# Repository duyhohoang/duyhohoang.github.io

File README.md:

# Hardware Lab portfolio

Existing black-and-pink portfolio for PCB Design, Embedded Systems and IoT. Next.js App Router, React, TypeScript and Motion. Self-hosted fonts and local imagery; no backend, API, database, server actions or runtime Node server.

## Local development

Use Node **24.19.0** (`.node-version`) and **pnpm 11.25.0** (`packageManager`).

```sh
pnpm install --frozen-lockfile
pnpm dev
```

Development: http://127.0.0.1:3000. For production:

```sh
pnpm lint
pnpm test
pnpm build
pnpm check:export
pnpm preview
```

Static preview: http://127.0.0.1:3001. Deploy only `out/`. `next.config.ts` already preserves export, trailing slashes, unoptimized local images and disabled framework header. The postbuild helper preserves Windows-generated Next segment payload aliases; it is harmless on Linux.

## Public configuration

Copy `.env.example` to `.env.local` if overriding defaults. `src/data/contact.ts` contains the owner-provided public email, `hoangduy2206.ute@gmail.com`. `NEXT_PUBLIC_CONTACT_EMAIL` overrides it; an explicitly empty value disables composition and shows a configuration warning. Public variables are embedded at build time and must never contain secrets.

The contact form validates fields and composes a safely encoded `mailto:` draft. Visitors finish sending in their own email app. No delivery is performed or reported by this website. A direct **Send Email** link works without JavaScript; form submission is disabled until hydration to avoid leaking form fields into a GET URL.

Set `NEXT_PUBLIC_SITE_URL` to your real HTTPS Pages origin or custom domain and rebuild before enabling search indexing. Without it, the local preview intentionally emits noindex/disallow and localhost canonical/sitemap URLs.

## GitHub Pages production

The selected address is **https://duyhohoang.github.io/**, published from repository `duyhohoang.github.io`. The included GitHub Actions workflow builds and deploys only `out/` on main pushes. Enable **Settings → Pages → Source: GitHub Actions** in that repository. See [DEPLOY.md](DEPLOY.md) for setup and validation.

## Alternative Cloudflare deployment

For the current Workers project, `wrangler.jsonc` explicitly serves static files from `out/`; build with `pnpm build` and deploy with `npx wrangler@4.151.3 deploy`. No OpenNext migration or runtime server is needed.

For the alternative Pages workflow, see [DEPLOY.md](DEPLOY.md) for GitHub connection, build settings, free Pages address, custom domain and automatic deploys. Use the **Next.js (Static HTML Export)** preset, `pnpm build`, output `out`, production branch `main`. This is prepared locally, not publicly deployed.

## Implementation and validation

- `src/components/PortfolioHome.tsx`: existing homepage sections and content.
- `src/components/backgrounds/CircuitBackground.tsx`: SVG decoration; visibility-aware CSS pulses, static on mobile/reduced motion.
- `src/hooks/usePortfolioMotion.ts`: one shared reveal observer and finite animations, with lifecycle cleanup.
- `src/components/ContactForm.tsx`, `src/lib/contact.ts`: validated email draft composition.
- `src/data/portfolio-media.ts`: replaceable local portrait and hardware media.
- `scripts/review-fidelity.mjs`: twelve reference-sized production screenshots.
- `scripts/test-animations.mjs`: production interactions, motion, six viewport widths, navigation cleanup and no-JS checks.
- `docs/PHASE4-REPORT.md`: validation evidence and remaining limitations.

Project studies remain illustrative, with validation status identified. No employment, education, manufacturing results or client metrics have been invented.

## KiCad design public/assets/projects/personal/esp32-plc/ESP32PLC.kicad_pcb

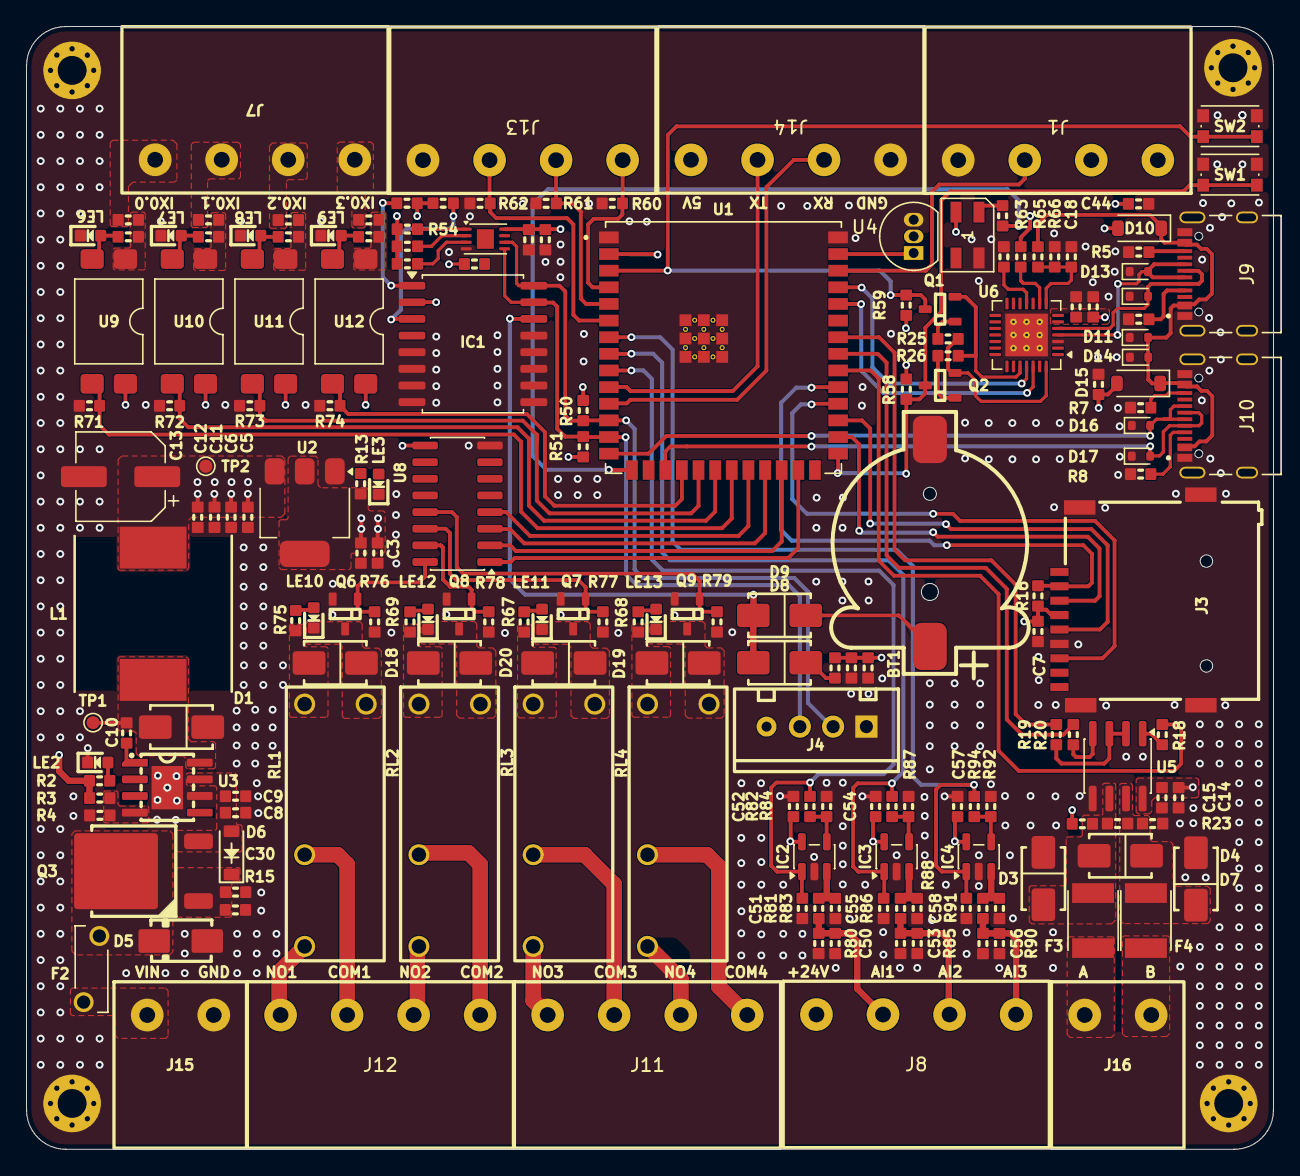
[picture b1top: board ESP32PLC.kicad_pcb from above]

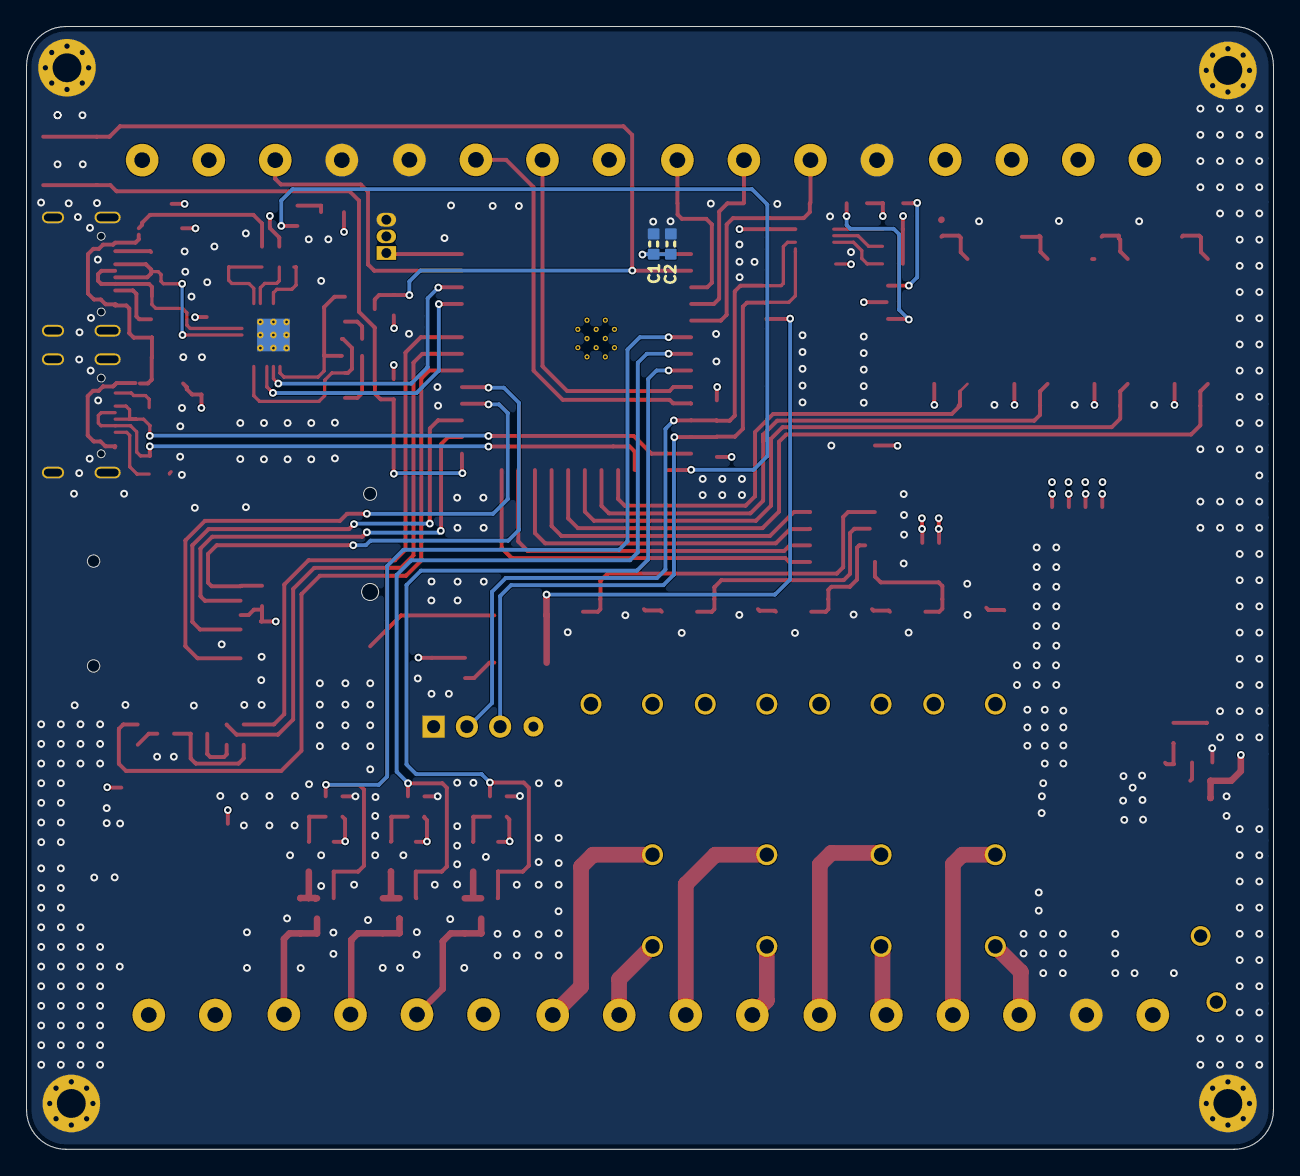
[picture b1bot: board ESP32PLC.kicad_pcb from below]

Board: 4 copper layers, 95.2 x 85.7 mm, 190 parts (2 on the bottom side), 117 nets.

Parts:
BT1: Battery_Cell; BatteryHolder_CR1220
C1, C3, C6, C16, C41, C43, C46, C47, C48, C49, C50, C51, C53, C55, C56, C58: 100nF/0603/50V; C_0603
C2, C4, C5, C17: 10uF/0603/6.3V; C_0603
C7, C15: 100nF/50V/0603; C_0603
C8, C9: 4.7uF/50V/0603; C_0603
C10, C12: 10uF/50V/0603; C_0603
C11, C14: 10uF/6.3V/0603; C_0603
C13: 220uF/6.3V/6.3x5.4; CP_Elec_6.3x5.4
C18: 1uF/0603/6.3V; C_0603
C30, C40, C42, C52, C54, C57: 1uF/0603/50V; C_0603
C44, C45: 10uF/0603/50V; C_0603
D1: SS54/5A/40V; D_SMA_TVS
D2: SK6812MINI; LED_SK6812MINI_PLCC4_3.5x3.5mm_P1.75mm
D3, D4, D7: D_TVS; D_SMA_TVS
D5: SMAJ281-E3/61; D_SMA
D6: BZT52H-C5V1; SOD-123
D8, D9, D18, D19, D20, D21: D_Diode; D_SMA_TVS
D10, D15: D_Schottky; D_SOD-123
D11, D12, D13, D14, D16, D17: LESD5D5.0CT1G; D_SOD-523
F2: RUEF250/30V/2.5A; FUSRR505W81L660T250H1360
F3, F4: Polyfuse; FUSER_MF-MSMF075_24-2
H1, H2, H3, H4: MountingHole_Pad; MountingHole_2.2mm_M2_Pad_Via
IC1: RTC_DS3231M; SOIC-16W_7.5x10.3mm_P1.27mm
IC2, IC3, IC4: TP5551-TR; SOT-23-5
J1, J7, J8, J11, J12, J13, J14: Screw_Terminal_01x04; KF-5.08-4P
J3: Micro_SD_Card_Det1; MicroSD_Socket_9P
J4: Conn_01x04_Pin; Conn_XH-P2.54mm-4P
J9, J10: TYPE-C-31-M-12; HRO_TYPE-C-31-M-12
J15, J16: Screw_Terminal_01x02; KF-5.08-2P
L1: 22uH/CDRH127-220; INDPM120120X800N
LE2, LE3, LE6, LE7, LE8, LE9, LE10, LE11, LE12, LE13: RED/0603; LED_0603
Q1, Q2: NPN; SOT23-3
Q3: P_Mosfet; TO-252-2
Q6, Q7, Q8, Q9: N_Mosfet; SOT23-3
R2, R13, R67, R68, R69, R75: 1K/0603/1%; R_0603
R3, R15, R16, R21, R23, R24, R25, R26, R58, R59, R63, R64, R71, R72, R73, R74, R80, R85, R90: 10K/0603/1%; R_0603
R4: 3.3K/0603/1%; R_0603
R5, R6, R7, R8: 5.1K/0603/1%; R_0603
R9, R10, R11, R12: 4.7K/0603/1%; R_0603
R17: 0R/0603/1%; R_0603
R18, R19, R20, R22: 120R/0603/1%; R_0603
R50, R51, R52, R53, R54, R55, R56, R57: 4K7/0603/1%; R_0603
R60, R61, R62: 165R/0603/1%; R_0603
R65: 22.1R/0603/50V; R_0603
R66: 47.5K/0603/50V; R_0603
R76, R77, R78, R79: 1M/0603/1%; R_0603
R81, R82, R83, R84, R86, R87, R88, R89, R91, R92, R93, R94: 100K/0603/1%; R_0603
RL1, RL2, RL3, RL4: Relay_G5NB-1A-E_DC5; Relay_G5NB-1A-E DC5
SW1, SW2: SW_Push; SW_Push_1P1T_NO_CK_KMR2
TP1, TP2: TestPoint; TestPoint_Pad_D1.0mm
U1: ESP32-S3-WROOM-1U-N8R8; XCVR_ESP32-S3-WROOM-1U-N8R8
U2: AMS1117-3.3; SOT-223-3_TabPin2
U3: TPS5430DDA; SOIC8E(EXPOSED PAD)
U4: LM35-LP; TO-92_Inline
U5: SP3485CN; SOIC-8_3.9x4.9mm_P1.27mm
U6: CP2102N-Axx-xQFN28; QFN-28-1EP_5x5mm_P0.5mm_EP3.25x3.25mm_ThermalVias
U7: 24LC512_IPC; DFN-8-1EP_3x2mm_P0.5mm_EP1.3x1.5mm
U8: ULN2003; SOIC-16_3.9x9.9mm_P1.27mm
U9, U10, U11, U12: Opto; SMDIP-4_W9.53mm_Clearance8mm

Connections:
+3.3V: C1.1, C2.1, C3.1, C4.1, C7.1, C14.1, C15.1, C16.1, C17.1, C42.1, C43.1, C52.1, C54.1, C57.1, D2.4 (VDD), IC2.5 (V+), IC3.5 (V+), IC4.5 (V+), J1.1, J1.2, J3.4 (VDD), R13.1, R16.1, R21.1, R58.1, R59.1, R63.1, U1.2 (3V3), U2.2 (VO), U5.8 (VCC), U6.6 (VDD), U6.7 (VREGIN), U7.8 (VCC), U9.4, U10.4, U11.4, U12.4
+5V: C5.1, C6.1, C11.1, C12.1, C13.1, C40.1, C41.1, C44.1, C45.1, D10.2, D15.2, D18.2, D19.2, D20.2, D21.2, IC1.2 (VCC), J4.4, J14.4, L1.2, R2.1, R3.1, R24.1, R50.1, R51.1, R52.2, R53.1, R54.1, R55.2, R56.2, R57.2, R67.1, R68.1, R69.1, R75.1, RL1.1, RL2.1, RL3.1, RL4.1, TP2.1 (1_1), U2.3 (VI), U4.2 (V_{OUT}), U8.9 (COM)
+24V: F2.2, J8.1, J15.1
/32K: IC1.1 (32KHZ), R53.2
/%IW0.0: J13.1, R60.1, U1.4 (IO4)
/%IW0.1: J13.2, R61.1, U1.5 (IO5)
/%IW0.2: J13.3, R62.1, U1.6 (IO6)
/%IX0.0: R71.1, U1.21 (IO13), U9.3
/%IX0.1: R72.1, U1.20 (IO12), U10.3
/%IX0.2: R73.1, U1.19 (IO11), U11.3
/%IX0.3: R74.1, U1.18 (IO10), U12.3
/%QX0.0: U1.25 (IO48), U8.1 (I1)
/%QX0.1: U1.24 (IO47), U8.2 (I2)
/%QX0.2: U1.23 (IO21), U8.3 (I3)
/%QX0.3: U1.22 (IO14), U8.4 (I4)
/A485: F3.2, J16.1
/AI1: C50.1, J8.2, R80.2, R81.1
/AI2: C53.1, J8.3, R85.2, R86.1
/AI3: C56.1, J8.4, R90.2, R91.1
/B485: F4.2, J16.2
/CC1: J9.A5 (CC1), R6.2
/CC2: J9.B5 (CC2), R5.2
/CC3: J10.A5 (CC1), R8.2
/CC4: J10.B5 (CC2), R7.2
/CHIP_PU: Q1.3 (C), R59.2, SW2.2, U1.3 (EN)
/CS: J3.2 (DAT3/CD), R16.2, U1.31 (IO38)
/DE_RE: R19.1, U1.34 (IO41)
/DTR: Q2.2 (E), R25.1, U6.28 (~DTR)
/GPIO0: Q2.3 (C), R58.2, SW1.2, U1.27 (IO0)
/GPIO1: U1.39 (IO1), U4.1 (+V_{S})
/GPIO2: J1.3, U1.38 (IO2)
/GPIO3: R17.1, U1.15 (IO3)
/GPIO7: C58.1, IC4.1 (OUT), R94.1, U1.7 (IO7)
/GPIO15: C55.1, IC3.1 (OUT), R89.1, U1.8 (IO15)
/GPIO16: C51.1, IC2.1 (OUT), R84.1, U1.9 (IO16)
/GPIO19: D17.2 (A2), J10.A7 (DN1), J10.B7 (DN2), U1.17 (IO9)
/GPIO20: D16.2 (A2), J10.A6 (DP1), J10.B6 (DP2), U1.14 (IO20)
/MISO: J3.7 (DAT0), U1.30 (IO37)
/MOSI: J3.3 (CMD), U1.28 (IO35)
/OUT1: J7.4, R9.1
/OUT2: J7.3, R10.1
/OUT3: J7.2, R11.1
/OUT4: J7.1, R12.1
/RGB_CTRL: D2.3 (DIN), R17.2
/RLAY1A: J12.1, RL1.3
/RLAY1B: J12.2, RL1.2
/RLAY2A: J12.3, RL2.3
/RLAY2B: J12.4, RL2.2
/RLAY3A: J11.1, RL3.3
/RLAY3B: J11.2, RL3.2
/RLAY4A: J11.3, RL4.3
/RLAY4B: J11.4, RL4.2
/RLY1: Q6.1 (G), R76.1, U8.16 (O1)
/RLY2: Q8.1 (G), R78.1, U8.15 (O2)
/RLY3: Q7.1 (G), R77.1, U8.14 (O3)
/RLY4: Q9.1 (G), R79.1, U8.13 (O4)
/RTS: Q1.2 (E), R26.1, U6.24 (~RTS)
/RX2: J14.2, U1.11 (IO18)
/RX485: R18.1, U1.32 (IO39)
/SCK: J3.5 (CLK), U1.29 (IO36)
/SCL: IC1.16 (SCL), J4.2, R50.2, U1.12 (IO8), U7.6 (SCL)
/SDA: IC1.15 (SDA), J4.3, R51.2, U1.13 (IO19), U7.5 (SDA)
/SQW: IC1.3 (~INT/SQW), R54.2
/TX2: J14.3, U1.10 (IO17)
/TX485: R20.1, U1.33 (IO40)
/U0RXD: U1.37 (TXD0), U6.25 (RXD)
/U0TXD: U1.36 (RXD0), U6.26 (TXD)
/USB_DN: D12.2 (A2), J9.A7 (DN1), J9.B7 (DN2), U6.5 (D-)
/USB_DP: D13.2 (A2), J9.A6 (DP1), J9.B6 (DP2), U6.4 (D+)
GND: BT1.2 (-), C1.2, C2.2, C3.2, C4.2, C5.2, C6.2, C7.2, C8.2, C9.2, C11.2, C12.2, C13.2, C14.2, C15.2, C16.2, C17.2, C18.2, C30.2, C40.2, C41.2, C42.2, C43.2, C44.2, C45.2, C50.2, C51.2, C52.2, C53.2, C54.2, C55.2, C56.2, C57.2, C58.2, D1.1, D2.2 (VSS), D3.1 (A1), D5.1 (A1), D7.2 (A2), D11.1 (A1), D12.1 (A1), D13.1 (A1), D14.1 (A1), D16.1 (A1), D17.1 (A1), H1.1 (1_1), H2.1 (1_1), H3.1 (1_1), H4.1 (1_1), IC1.5 (GND), IC1.6 (GND), IC1.7 (GND), IC1.8 (GND), IC1.9 (GND), IC1.10 (GND), IC1.11 (GND), IC1.12 (GND), IC1.13 (GND), IC2.2 (V-), IC3.2 (V-), IC4.2 (V-), J1.4, J3.6 (VSS), J3.10 (SHIELD), J4.1, J9.A1_B12 (GND), J9.B1_A12 (GND), J9.S1 (SHIELD), J9.S2 (SHIELD), J9.S3 (SHIELD), J9.S4 (SHIELD), J10.A1_B12 (GND), J10.B1_A12 (GND), J10.S1 (SHIELD), J10.S2 (SHIELD), J10.S3 (SHIELD), J10.S4 (SHIELD), J13.4, J14.1, J15.2, LE2.2, LE3.2, LE6.2, LE7.2, LE8.2, LE9.2, Q6.2 (S), Q7.2 (S), Q8.2 (S), Q9.2 (S), R4.2, R5.1, R6.1, R7.1, R8.1, R15.2, R23.2, R60.2, R61.2, R62.2, R64.2, R66.2, R71.2, R72.2, R73.2, R74.2, R76.2, R77.2, R78.2, R79.2, R80.1, R82.1, R83.2, R85.1, R87.1, R88.2, R90.1, R92.1, R93.2, SW1.1, SW2.1, U1.1 (GND), U1.40 (GND), U1.41_1 (GND), U1.41_2 (GND), U1.41_3 (GND), U1.41_4 (GND), U1.41_5 (GND), U1.41_6 (GND), U1.41_7 (GND), U1.41_8 (GND), U1.41_9 (GND), U2.1 (GND), U3.6 (GND), U3.9 (GNDPAD), U4.3 (GND), U5.5 (GND), U6.3 (GND), U6.29 (GND), U7.4 (GND), U8.8 (GND)
unnamed: BT1.1 (+), D9.1
unnamed: C46.1, R9.2, U9.1
unnamed: C46.2, LE6.1, U9.2
unnamed: C47.1, R10.2, U10.1
unnamed: C47.2, LE7.1, U10.2
unnamed: C48.1, R11.2, U11.1
unnamed: C48.2, LE8.1, U11.2
unnamed: C49.1, R12.2, U12.1
unnamed: C49.2, LE9.1, U12.2
unnamed: D3.2 (A2), D4.2 (A2), F3.1, R21.2, R22.1, U5.6 (A)
unnamed: D4.1 (A1), D7.1 (A1), F4.1, R22.2, R23.1, U5.7 (B)
unnamed: D5.2 (A2), F2.1, Q3.3 (D)
unnamed: C30.1, D6.2 (A), Q3.1 (G), R15.1
unnamed: C8.1, C9.1, D6.1 (K), Q3.2 (S), U3.7 (VIN)
unnamed: D8.1, R24.2
unnamed: D8.2, D9.2, IC1.14 (VBAT)
unnamed: IC2.3 (+IN), R81.2, R83.1
unnamed: IC2.4 (-IN), R82.2, R84.2
unnamed: IC3.3 (+IN), R86.2, R88.1
unnamed: IC3.4 (-IN), R87.2, R89.2
unnamed: IC4.3 (+IN), R91.2, R93.1
unnamed: IC4.4 (-IN), R92.2, R94.2
unnamed: LE2.1, R2.2
unnamed: LE3.1, R13.2
unnamed: LE10.1, R75.2
unnamed: LE11.1, R67.2
unnamed: LE12.1, R69.2
unnamed: LE13.1, R68.2
unnamed: Q1.1 (B), R25.2
unnamed: Q2.1 (B), R26.2
unnamed: D18.1, LE10.2, Q6.3 (D), RL1.4
unnamed: D19.1, LE11.2, Q7.3 (D), RL3.4
unnamed: D20.1, LE12.2, Q8.3 (D), RL2.4
unnamed: D21.1, LE13.2, Q9.3 (D), RL4.4
unnamed: C10.2, U3.1 (BOOT)
unnamed: C10.1, D1.2, L1.1, TP1.1 (1_1), U3.8 (PH)
unnamed: R3.2, R4.1, U3.4 (VSENSE)
unnamed: R19.2, U5.2 (~RE), U5.3 (DE)
unnamed: R20.2, U5.4 (DI)
unnamed: R18.2, U5.1 (RO)
unnamed: C18.1, R65.2, R66.1, U6.8 (VBUS)
unnamed: R63.2, U6.9 (~RST)
unnamed: R64.1, U6.11 (~SUSPEND)
unnamed: R57.1, U7.1 (A0)
unnamed: R56.1, U7.2 (A1)
unnamed: R55.1, U7.3 (A2)
VBUS: D10.1, D11.2 (A2), D14.2 (A2), D15.1, J9.A4_B9 (VBUS), J9.B4_A9 (VBUS), J10.A4_B9 (VBUS), J10.B4_A9 (VBUS), R65.1

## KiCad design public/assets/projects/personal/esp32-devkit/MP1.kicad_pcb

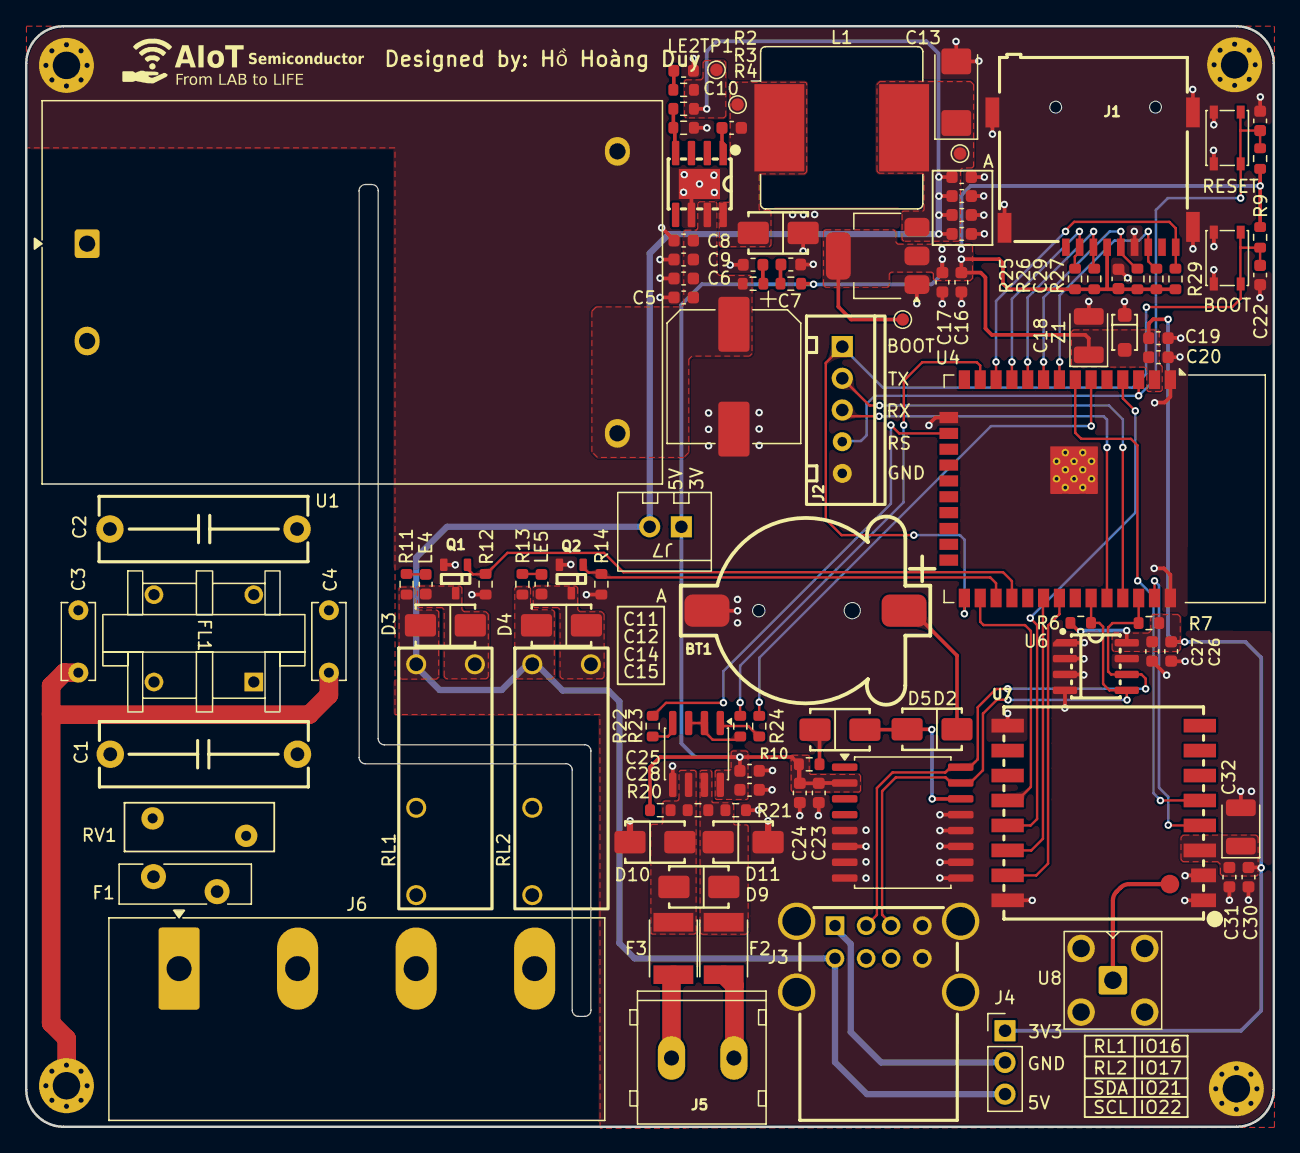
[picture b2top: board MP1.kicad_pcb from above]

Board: 2 copper layers, 100.0 x 88.2 mm, 109 parts (0 on the bottom side), 56 nets.

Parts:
BOOT: SW_Push/4.2X3.2X2.5; SW_SPST_PTS810
BT1: Battery_Cell; BatteryHolder_CR1220
C1: 100nF/275VAC; C_Rect_L16.5mm_W5.0mm_P15.00mm_MKT
C2: 0.1uF/275VAC; C_Rect_L16.5mm_W5.0mm_P15.00mm_MKT
C3, C4: 10nF/1000VAC; C_Disc_D6.0mm_W2.5mm_P5.00mm
C5, C10, C12, C24, C28: 10uF/50V/0603; C_0603_1608Metric
C6, C15, C17, C20, C21, C22, C27, C29, C31: 100nF/50V/0603; C_0603_1608Metric
C7: 220uF/10x10.5/50V; CP_Elec_10x10.5
C8, C9: 4.7uF/50V/0603; C_0603_1608Metric
C11, C14, C16, C19, C23, C25, C26, C30: 10uF/6.3V/0603; C_0603_1608Metric
C13: 220uF/6.3V/2312; CP_EIA-6032-15_Kemet-U
C18, C32: 100uF/6.3V/1411; CP_EIA-3528-12_Kemet-T
D1: SS54/5A/40V; D_SMA_TVS
D2, D3, D4, D5: D_Diode; D_SMA_TVS
D9, D10, D11: D_TVS; D_SMA_TVS
F1: GR250-500; Fuse_Bourns_MF-RG500
F2, F3: Polyfuse; FUSER_MF-MSMF075_24-2
FL1: UU9.8/10mH; ACFilterChokeUU9.8
H1, H2, H3, H4: MountingHole_Pad; MountingHole_2.2mm_M2_Pad_Via
IC1: RTC_DS3231M; SOIC-16W_7.5x10.3mm_P1.27mm
J1: Micro_SD_Card_Det1; MicroSD_Socket_9P
J2: Conn_01x05_Pin; Conn_XH-P2.54mm-5P
J3: USB_A_Stacked; USB_A_Wuerth_61400826021_Horizontal_Stacked
J4: Conn_01x03_Pin; PinHeader_1x03_P2.54mm_Vertical
J5: Screw_Terminal_01x02; KF128-5.0-2P
J6: Screw_Terminal_01x04; TerminalBlock_Ningbo-Kagnex_HB9500M_1x04_P9.5mm
J7: Conn_01x02_Pin; XH 2.54 2Pin Female
L1: 22uH/CDRH127-220; L_Bourns_SRR1208_12.7x12.7mm
LE1, LE2, LE3, LE4, LE5: RED/0603; L_0603_1608Metric
LOGO: AIoT_Semiconductor_Smooth
Q1, Q2: N_Mosfet; SOT23-3
R1: 2.2K/0603/5%; R_0603_1608Metric
R2, R10, R11, R13: 1K/0603/1%; R_0603_1608Metric
R3, R8, R9, R20, R21, R25, R27, R29: 10K/0603/1%; R_0603_1608Metric
R4: 3.3K/0603/1%; R_0603_1608Metric
R5: 2.2K/0603/1%; R_0603_1608Metric
R6, R7: 4K7/0603/1%; R_0603_1608Metric
R12, R14: 1M/0603/1%; R_0603_1608Metric
R19, R22, R23, R24, R26, R28: 120R/0603/1%; R_0603_1608Metric
RESET: SW_Push/4.2X3.2X2.5; SW_SPST_PTS810
RL1, RL2: Relay_G5NB-1A-E_DC5; Relay_G5NB-1A-E DC5
RV1: 10D751K; RV_Disc_D12mm_W3.9mm_P7.5mm
TP1, TP2, TP3, TP4: TestPoint; TestPoint_Pad_D1.0mm
U1: HLK-10M24; Converter_ACDC_Hi-Link_HLK-10Mxx
U2: TPS5430DDA; SOIC8E(EXPOSED PAD)
U3: AMS1117-3.3; SOT-223-3_TabPin2
U4: ESP32-WROOM-32D
U5: SP3485CN; SOIC-8_3.9x4.9mm_P1.27mm
U6: 24LC512_IPC; SOIC-8_3.9x4.9mm_P1.27mm
U7: Ai-Thinker-Ra-02; MODULE_RA-02_LORA
U8: Ipex; SMA-KWE-Z001
Z1: D_Zener_IPC; D_SOD-123F_IPC

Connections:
+3.3V: C16.1, C17.1, C18.1, C19.1, C20.1, C23.1, C24.1, C25.1, C26.1, C27.1, C28.1, C29.1, C30.1, C31.1, C32.1, IC1.2 (VCC), J1.4 (VDD), J4.1, J7.1, R5.1, R6.1, R7.1, R8.1, R9.1, R10.1, R20.1, R25.1, R26.1, R27.1, R28.1, R29.1, TP4.1 (1_1), U3.2 (VO), U4.2 (VDD), U5.8 (VCC), U6.8 (VCC), U7.3 (VDD), Z1.2
+5V: C11.1, C12.1, C13.1, C14.1, C15.1, D3.2, D4.2, J3.5 (VBUS2), J4.3, J7.2, L1.2, R2.1, R3.1, R11.1, R13.1, RL1.1, RL2.1, TP2.1 (1_1), TP3.1 (1_1), U3.3 (VI)
+24V: C5.1, C6.1, C7.1, C8.1, C9.1, R1.1, U1.4 (+Vout), U2.7 (VIN)
/Project Architecture/EEPROM/UD.IO21.I2C_SCL: IC1.16 (SCL), J3.2 (D1-), R7.2, U4.36 (IO22), U6.6 (SCL)
/Project Architecture/EEPROM/UD.IO22.I2C_SDA: IC1.15 (SDA), J3.3 (D1+), R6.2, U4.33 (IO21), U6.5 (SDA)
/Project Architecture/ESP WROOM 32E/BOOT: BOOT.2, C22.1, J2.1, R9.2, U4.25 (IO0)
/Project Architecture/ESP WROOM 32E/ESP_RXD0: J2.3, U4.34 (RXD0/IO3)
/Project Architecture/ESP WROOM 32E/ESP_TXD0: J2.2, U4.35 (TXD0/IO1)
/Project Architecture/ESP WROOM 32E/LORA_INT: U4.7 (IO35), U7.5 (DIO0)
/Project Architecture/ESP WROOM 32E/LORA_MISO: U4.4 (SENSOR_VP), U7.13 (MISO)
/Project Architecture/ESP WROOM 32E/LORA_MOSI: U4.30 (IO18), U7.14 (MOSI)
/Project Architecture/ESP WROOM 32E/LORA_NSS: U4.31 (IO19), U7.15 (~NSS)
/Project Architecture/ESP WROOM 32E/LORA_RST: U4.37 (IO23), U7.4 (~RESET)
/Project Architecture/ESP WROOM 32E/LORA_SCK: U4.26 (IO4), U7.12 (SCK)
/Project Architecture/ESP WROOM 32E/RESET: C21.1, J2.4, R8.2, RESET.2, U4.3 (EN)
Earth: C3.2, C4.1, H3.1 (1_1)
GND: BOOT.1, BT1.2 (-), C5.2, C6.2, C7.2, C8.2, C9.2, C11.2, C12.2, C13.2, C14.2, C15.2, C16.2, C17.2, C18.2, C19.2, C20.2, C21.2, C22.2, C23.2, C24.2, C25.2, C26.2, C27.2, C28.2, C29.2, C30.2, C31.2, C32.2, D1.1, D10.1 (A1), D11.2 (A2), H1.1 (1_1), H2.1 (1_1), H4.1 (1_1), IC1.5 (GND), IC1.6 (GND), IC1.7 (GND), IC1.8 (GND), IC1.9 (GND), IC1.10 (GND), IC1.11 (GND), IC1.12 (GND), IC1.13 (GND), J1.6 (VSS), J1.10 (SHIELD), J2.5, J3.4 (GND1), J3.8 (GND2), J3.9 (Shield), LE1.2, LE2.2, LE3.2, Q1.2 (S), Q2.2 (S), R4.2, R12.2, R14.2, R21.2, RESET.1, U1.3 (-Vout), U2.6 (GND), U2.9 (GNDPAD), U3.1 (GND), U4.1 (GND), U4.15 (GND), U4.38 (GND), U4.39 (GND), U5.5 (GND), U6.1 (A0), U6.2 (A1), U6.3 (A2), U6.4 (GND), U6.7 (WP), U7.1 (GND), U7.2 (GND), U7.9 (GND), U7.16 (GND), U8.2, Z1.1
IO25/SPI_MOSI: J1.3 (CMD), R26.2, U4.10 (IO25)
IO26/SPI_CS: J1.2 (DAT3/CD), R25.2, U4.11 (IO26)
IO27/SPI_DET: J1.9 (DET), R29.2, U4.12 (IO27)
IO32/SPI_MISO: J1.7 (DAT0), R28.2, U4.8 (IO32)
IO33/SPI_SCK: J1.5 (CLK), R27.2, U4.9 (IO33)
LINE: F1.1, J6.1
NEUTRAL: C1.2, FL1.1, J6.2, RL1.2, RL2.2, RV1.1
unnamed: BT1.1 (+), D2.1
unnamed: C1.1, F1.2, FL1.3, RV1.2
unnamed: D5.1, R10.2
unnamed: D9.2 (A2), D10.2 (A2), F3.1, R19.1, R20.2, U5.6 (A)
unnamed: D9.1 (A1), D11.1 (A1), F2.1, R19.2, R21.1, U5.7 (B)
unnamed: D2.2, D5.2, IC1.14 (VBAT)
unnamed: J3.1 (VBUS1), J4.2
unnamed: LE1.1, R1.2
unnamed: LE2.1, R2.2
unnamed: LE3.1, R5.2
unnamed: LE4.1, R11.2
unnamed: LE5.1, R13.2
unnamed: D3.1, LE4.2, Q1.3 (D), RL1.4
unnamed: D4.1, LE5.2, Q2.3 (D), RL2.4
unnamed: C2.1, C4.2, FL1.2, U1.1 (AC/L)
unnamed: C2.2, C3.1, FL1.4, U1.2 (AC/N)
unnamed: C10.2, U2.1 (BOOT)
unnamed: C10.1, D1.2, L1.1, TP1.1 (1_1), U2.8 (PH)
unnamed: R3.2, R4.1, U2.4 (VSENSE)
unnamed: R23.2, U5.2 (~RE), U5.3 (DE)
unnamed: R22.2, U5.4 (DI)
unnamed: R24.2, U5.1 (RO)
unnamed: U7.17 (Anaten), U8.1
O.1: J6.3, RL1.3
O.2: J6.4, RL2.3
RL1: Q1.1 (G), R12.1, U4.28 (IO17)
RL2: Q2.1 (G), R14.1, U4.27 (IO16)
RS485_A: F3.2, J5.1
RS485_B: F2.2, J5.2
RS485_DE_RE: R23.1, U4.13 (IO14)
RS485_RX: R24.1, U4.6 (IO34)
RS485_TX: R22.1, U4.16 (IO13)

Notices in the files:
parts and their libraries:
Copyright 2021 Accelerated Designs. All rights reserved.
